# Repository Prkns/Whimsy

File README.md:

# Whimsy - Rev0.21

A 40% keyboard with exposed Elite-C/OLED and Rotary encoder.

My first attempt at designing a "proper" custom keyboard. I spent far too long looking at all the amazing new PCB's and custom keyboards being released and having a massive urge to do one for myself. Here is my first attempt.

I've not taken delivery of the physical PCBs as of yet so i can't comment on how well i did, but they will be with me shortly.

**STILL IN DEVELOPMENT - NOT READY FOR PRODUCTION - DO NOT ORDER**

---

### Plans 🤔

**rev1:** A working version of the board and an FR4 sandwich case

**rev2:** Tidied up traces and an acrylic case

---

#### Say hi 👋

If you're interested in any aspect of this board or want to point out anything that could be done better in a more private manner, head on over to my [website](https://prkns.me/) and you'll find a few different methods on there.

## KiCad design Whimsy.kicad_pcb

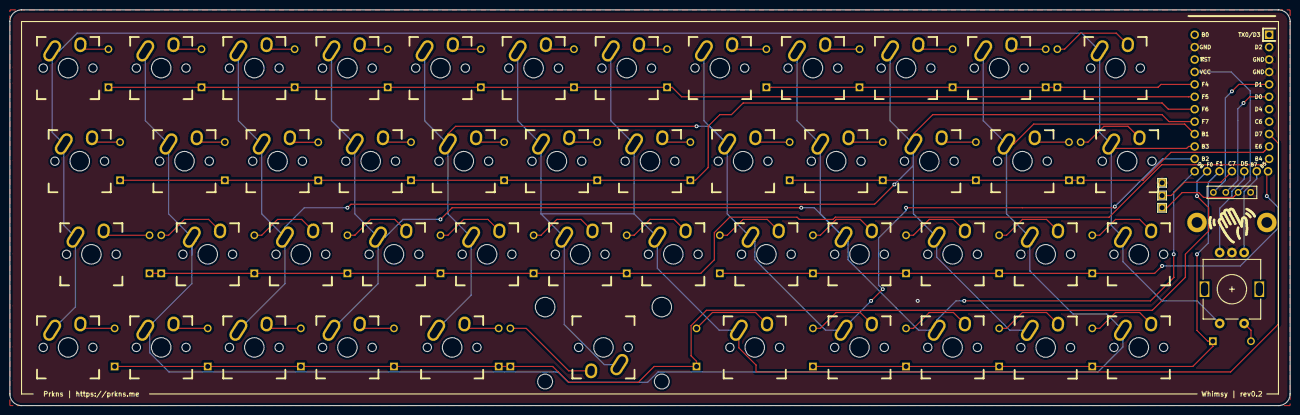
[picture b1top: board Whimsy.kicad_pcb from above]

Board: 2 copper layers, 261.9 x 81.0 mm, 102 parts (1 on the bottom side), 69 nets.

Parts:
D1, D2, D3, D4, D5, D6, D7, D8, D9, D10, D11, D12, D13, D14, D15, D16, D17, D18, D19, D20, D21, D22, D23, D24, D25, D26, D27, D28, D29, D30, D31, D32, D33, D34, D35, D36, D37, D38, D39, D40, D41, D42, D43, D44, D45, D46, D47, D48: D; Diode-Hybrid-Back
J1: OLED; OLED_4Pin
J2: LED Breakout; LED
K1, K4, K5, K6, K7, K8, K9, K10, K11, K12, K13, K14, K15, K16, K17, K18, K19, K21, K22, K23, K25, K26, K27, K29, K30, K31, K32, K33, K34, K35, K36, K37, K38, K39, K40, K41, K42, K43, K44, K47: KEYSW; Mx_Alps_100
K2, K20, K28, K46: KEYSW; Mx_Alps_125
K3, K45: KEYSW; Mx_Alps_150
K24: KEYSW; Mx_Alps_200
SW1: Rotary_Encoder_Switch; RotaryEncoder_Alps_EC11E-Switch_Vertical_H20mm-keebio_modif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
TH1, TH1#2: HOLE; M2_HOLE_PCB
U1: Elite-C; Elite-C-NoSilk
Wave: Wave

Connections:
GND: J1.4, J2.3, SW1.C, U1.3, U1.4, U1.23
LED: J2.2, U1.27
unnamed: D1.2, K1.2
unnamed: D2.2, K2.2
unnamed: D3.2, K3.2
unnamed: D4.2, K4.2
unnamed: D5.2, K5.2
unnamed: D6.2, K6.2
unnamed: D7.2, K7.2
unnamed: D8.2, K8.2
unnamed: D9.2, K9.2
unnamed: D10.2, K10.2
unnamed: D11.2, K11.2
unnamed: D12.2, K12.2
unnamed: D13.2, K13.2
unnamed: D14.2, K14.2
unnamed: D15.2, K15.2
unnamed: D16.2, K16.2
unnamed: D17.2, K17.2
unnamed: D18.2, K18.2
unnamed: D19.2, K19.2
unnamed: D20.2, K20.2
unnamed: D21.2, K21.2
unnamed: D22.2, K22.2
unnamed: D23.2, K23.2
unnamed: D24.2, K24.2
unnamed: D25.2, K25.2
unnamed: D26.2, K26.2
unnamed: D27.2, K27.2
unnamed: D28.2, K28.2
unnamed: D29.2, K29.2
unnamed: D30.2, K30.2
unnamed: D31.2, K31.2
unnamed: D32.2, K32.2
unnamed: D33.2, K33.2
unnamed: D34.2, K34.2
unnamed: D35.2, K35.2
unnamed: D36.2, K36.2
unnamed: D37.2, K37.2
unnamed: D38.2, K38.2
unnamed: D39.2, K39.2
unnamed: D40.2, K40.2
unnamed: D41.2, K41.2
unnamed: D42.2, K42.2
unnamed: D43.2, K43.2
unnamed: D44.2, K44.2
unnamed: D45.2, K45.2
unnamed: D46.2, K46.2
unnamed: D47.2, K47.2
unnamed: D48.2, SW1.S2
SCL: J1.2, U1.6
SDA: J1.1, U1.5
VCC: J1.3, J2.1, U1.21
col0: K1.1, K2.1, K3.1, K4.1, K45.1, K46.1, K47.1, SW1.S1, U1.15
col1: K5.1, K6.1, K7.1, K8.1, K41.1, K42.1, K43.1, K44.1, U1.16
col2: K9.1, K10.1, K11.1, K12.1, K37.1, K38.1, K39.1, K40.1, U1.17
col3: K13.1, K14.1, K15.1, K16.1, K33.1, K34.1, K35.1, K36.1, U1.13
col4: K17.1, K18.1, K19.1, K20.1, K29.1, K30.1, K31.1, K32.1, U1.14
col5: K21.1, K22.1, K23.1, K24.1, K25.1, K26.1, K27.1, K28.1, U1.9
rot0: SW1.A, U1.25
rot1: SW1.B, U1.26
row0: D1.1, D5.1, D9.1, D13.1, D17.1, D21.1, D25.1, U1.19
row1: D2.1, D6.1, D10.1, D14.1, D18.1, D22.1, D26.1, U1.18
row2: D3.1, D7.1, D11.1, D15.1, D19.1, D23.1, D27.1, U1.11
row3: D4.1, D8.1, D12.1, D16.1, D20.1, D24.1, D28.1, U1.29
row4: D29.1, D33.1, D37.1, D41.1, D45.1, U1.20
row5: D30.1, D34.1, D38.1, D42.1, D46.1, U1.10
row6: D31.1, D35.1, D39.1, D43.1, D47.1, U1.12
row7: D32.1, D36.1, D40.1, D44.1, D48.1, U1.28

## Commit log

2020-03-03 added elite-c, changed switch matrix to groups, added LED breakout, added off board reset switch, added OLED pins
2020-03-03 duplicate diode (D28) fixed
2020-03-03 first layout test
2020-03-03 README and Render
2020-03-04 properly laid out keys, cut edges
2020-03-04 added all diodes, new render, all cut corners
2020-03-05 updated readme and render
2020-03-05 started routing traces, finishing rev0.1
2020-03-05 better routing, columns, rows and via's to connect to the elite c
2020-03-05 added ignore
2020-03-05 updated ignorme
2020-03-05 removed redundancy
2020-03-05 first fully routed/traced board
2020-03-06 updated ignore
2020-03-06 gnd pins were not working as inteded, solder mask was a little off, fixed overall matrix, tightened the schematic to make it more logical
2020-03-06 flipped the elite-c, re-routed a lot of the board, tidied up some traces, new render, updated readme
2020-03-06 fixed gnd net
2020-03-06 issue with front mask
2020-03-07 rev0.2 production ready
2020-03-07 gerbers, directory management, file naming
2020-03-07 complete gerbers, bottom plate case, final renders, project clean-up
2020-03-19 updated renders
2020-03-19 case ideas
2020-03-19 rev0.3
2020-03-19 rev0.3 production ready
2020-04-05 Initial firmware
2020-04-05 updated PCB design
2020-10-13 removed v1 case files
2020-10-13 removed sandwich case
    in preparation for final release
2020-10-13 removed old renders
2020-10-13 new v0.3 PCB renders
